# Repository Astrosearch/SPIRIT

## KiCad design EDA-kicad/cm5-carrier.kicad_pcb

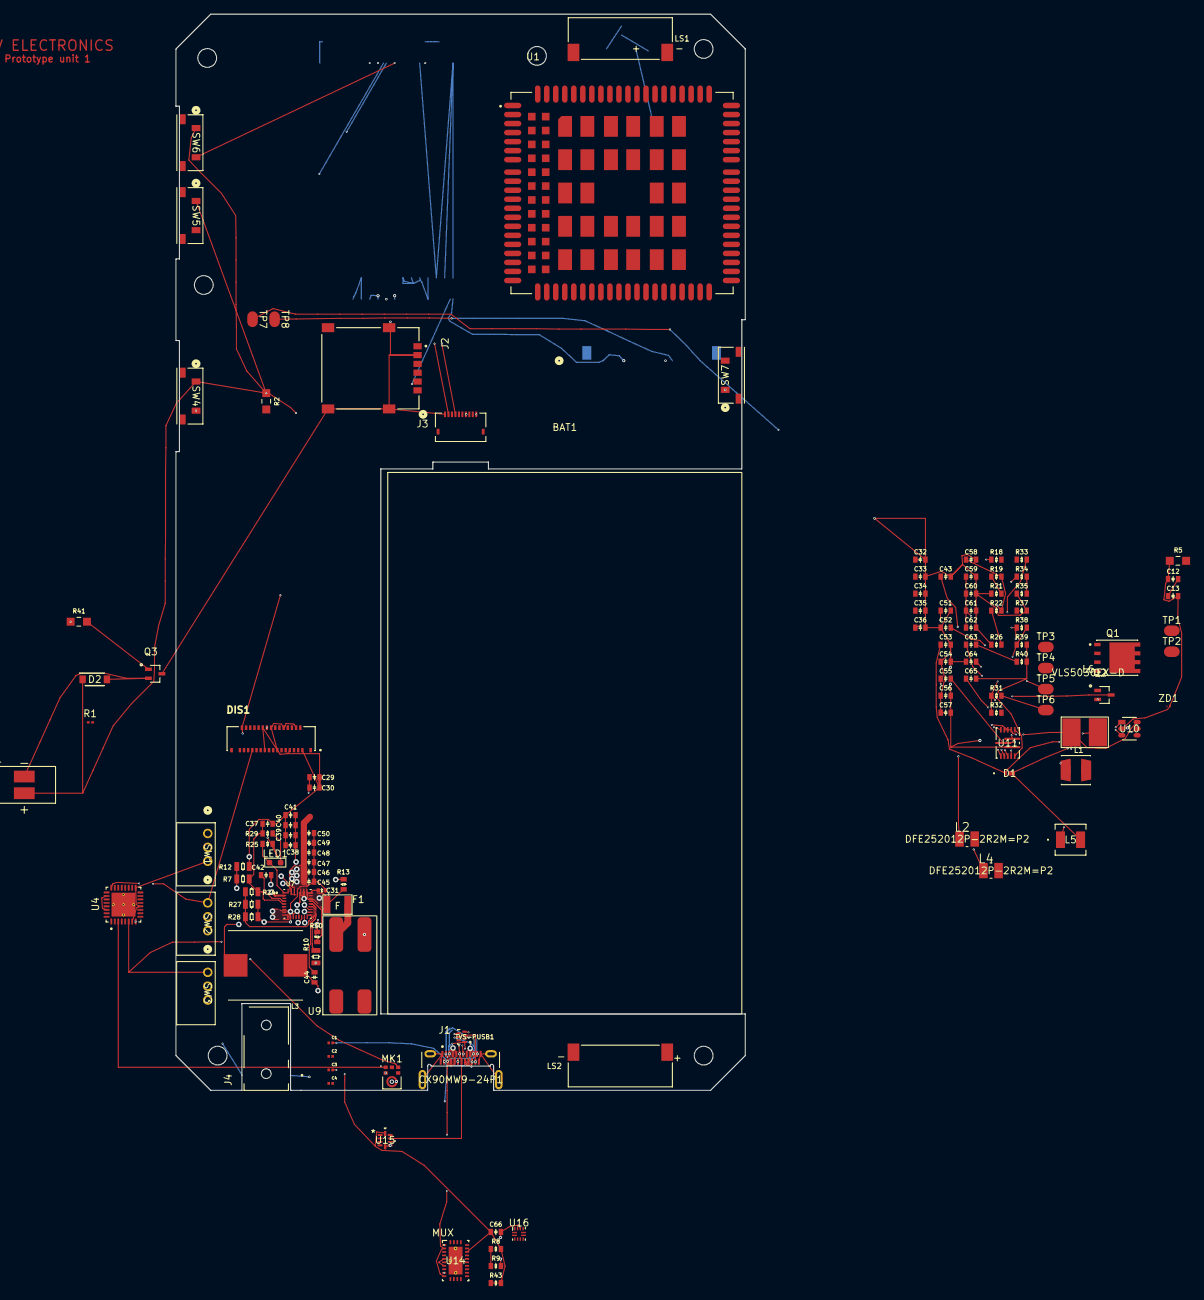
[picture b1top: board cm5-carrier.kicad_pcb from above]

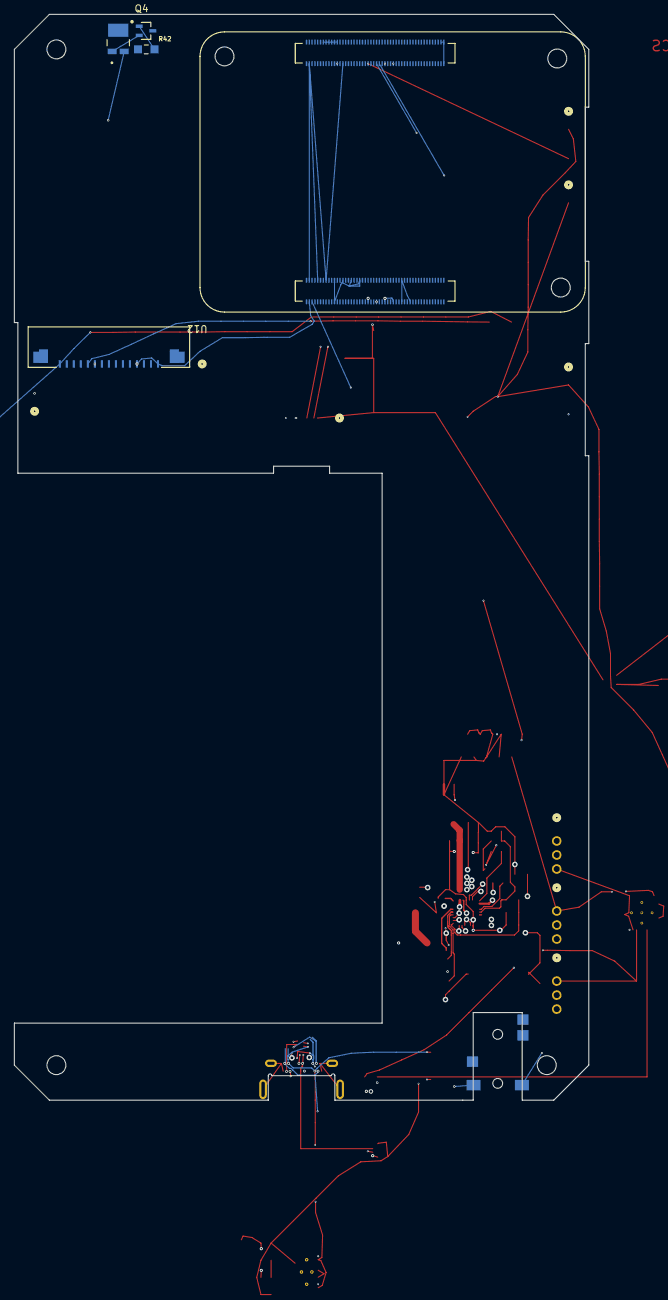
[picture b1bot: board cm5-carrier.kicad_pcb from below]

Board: 6 copper layers, 129 parts (5 on the bottom side), 118 nets.

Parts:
B1: VIBR; VIBRATION-PUI_HD-EMB1205-3-SC-R
BAT1: Li-ion-3.7 35Ah; battery_37V3500mAhLP685077JU
C1, C2, C3, C4: 0.33 µF coupling cap; USBC_capacitor_CAPC0603X33N
C12: 200pF; 0603-capacitor
C13, C38, C45, C55, C59, C66: 0.1uF; 0603-capacitor
C29, C30, C33, C34, C35, C39, C40, C41, C46, C47, C48, C49, C50: 10uF; 0603-capacitor
C31: 1nF 50V; 0402-capacitor
C32, C53, C54: 1uF; 0603-capacitor
C36, C43, C51, C56, C57, C58, C60, C61, C62, C65: 22uF; 0603-capacitor
C37, C52, C64: 4.7uF; 0603-capacitor
C42, C44: 47nF; 0603-capacitor
C63: 6.8nF; 0603-capacitor
D1: D_Schottky; schottky-diode-CR_DSN2_152AB-C_OSI
D2: 1N4007W-T; flyback-diode-SODFL3818X130N
DIS1: FH72-31S-0.3SHW; HRS_FH72-31S-0.3SHW
F1: 9A 6V; PTC RESET FUSE 9.0A 6V 1210 1210L900SLPR
J1: USBC-4-0-CX90MW9-24P1; USB-4-0-HIROSE_CX90MW9-24P1
J2: SIM-G85D1160022HHR; SIM-AMPHENOL_G85D1160022HHR
J3: FINGER; 10PIN
J4: SJ2-35894B-SMT-TR; 35mmJACK-CUI_SJ2-35894B-SMT-TR
L1: 3.3uH; 3-3uH-MURATA_LQH44PN3R3MPRL
L2, L4: 2.2uH; 2-2uH-inductor-INDC2520X120N
L3: 2.2uH; 2-2uh-inductorIND_ETQP4M2R2KVC
L5: 6.8uH; 6-8uH-inductor-LQH44PN6R8MPRLIND_LQH44PN_PR_MUR
L6: 1.5uH; 1-5uH-inductor-VLS5030EX-D
LED1: 5mA 2V Fv; LED-INDICATOR-RED-QBLP601-R5
LS1, LS2: CMR-15062S-67; SPEAKER_CMR-15062S-67
MK1: microphone; microphone_SPH0645LM4H-B
Module1: ComputeModule5-CM5; Raspberry-Pi-5-Compute-Module
Q1: NMOS-BSC0902NSIATMA1-PG-TDSON-8-6-IC_ISC037N03L5ISATMA1
Q2, Q3, Q4: gpio-driver-transistor-fix-SOT65P210X110-3N
R1: thermistor; thermistor-NTC0201Z_P63XP33_PAN
R2: 270KΩ 0.5W; 1K-05W-0805-RES_ERJP06J102V
R5: 100KΩ; 100K-0805-resistor-RES_ERA6AEB104V
R7: 127kΩ; 0805-resistor
R8, R9, R25, R30, R43: 10kΩ; 0603-resistor
R10: 4.7KΩ; 0805-resistor
R12: 100kΩ; 0805-resistor
R13: 100Ω; 0603-resistor
R18, R31, R32, R33: 100kΩ; 0603-resistor
R19: 680kΩ 1%; 0603-resistor
R21, R26: 470kΩ 1%; 0603-resistor
R22: 1MΩ 1%; 0603-resistor
R24: 5.23kΩ; 0805-resistor
R27: 10kΩ; 0805-resistor
R28: 30kΩ; 0805-resistor
R29: 680Ω; 0603-resistor
R34: 820kΩ; 0603-resistor
R35: 182KΩ; 0603-resistor
R37: 5Ω; 0603-resistor
R38: 750kΩ; 0603-resistor
R39: 200kΩ; 0603-resistor
R40: 6.8kΩ; 0603-resistor
R41, R42: 1KΩ 0.5W; 1K-05W-0805-RES_ERJP06J102V
SW1: EG25-switch-CSS-1210MC; privacy-switch-SW3_CSS-1210MC_NDC
SW2: MIC-switch-CSS-1210MC; privacy-switch-SW3_CSS-1210MC_NDC
SW3: CAM-switch-CSS-1210MC; privacy-switch-SW3_CSS-1210MC_NDC
SW4: PROG; buttonSW_TL3330_EWI
SW5: VOL-; buttonSW_TL3330_EWI
SW6: VOL+; buttonSW_TL3330_EWI
SW7: POW; buttonSW_TL3330_EWI
TP1, TP2, TP3, TP4, TP5, TP6, TP7, TP8: test-pad-1
TVS-PUSB1: TVS-array-IC_PUSB3AB6Z
U1: EG25GGC-128-SGNS; XCVR_EG25GGC-128-SGNS
U4: CODEC-TLV320AIC3204IRHBR; CODEC-QFN50P500X500X100-33N
U7: BQ25792RQMR; charger-bq25792-QFN40P400X400X100-29N
U9: BAT-CONNECTOR-FLTS22WR00
U10: 22V-boost-AP3032KTR-G1; SOT23-6_DIO
U11: MP3429GL-Z; QFN-3x4_MP3429_MNP
U12: FPC15pin-1mm-pitch-F52Q-1A7H1-11015; FPC15pin-1mm-pitch-CONN_F52Q-1A7H1-11015_AMP
U13: Flash-LED-Lumiled; LUMILED-DIODFN449X305X210-3N
U14: MUX HD3SS460RHRR; USB-MUX-RHR0028A
U15: USB SWITCH 2CHANNEL TS3USB221AQRSERQ1; USB-SWITCH-2CHANNEL-TS3USB221AQRSERQ1
U16: usb-polarity-TUSB321RWBR; polarity-usb-TUSB321RWBR
ZD1: protection-PESD5V0C1USFYL; USB-ESD-protection-diode-PESD5V0C1USFYL-SOD962-2_DSN0603-2_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

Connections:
1V8: DIS1.25, SW2.1, U4.24 (AVDD), U4.29 (DVDD)
3V3B: C66.1, DIS1.30, Module1.78 (GPIO_VREF(1.8v/3.3v_Input)), Q2.3 (S), R8.2, R25.2, R30.1, R31.1, R32.1, R33.2, R43.1, R43.2, SW3.1, U4.6 (IOVDD), U4.26 (LDOIN/HPVDD), U4.30 (LDO_SELECT), U14.22 (VCC), U15.10 (VCC)
5V: C59.1, C60.1, C61.1, C62.1, Module1.77 (+5v_(Input)), Module1.79 (+5v_(Input)), Module1.81 (+5v_(Input)), Module1.83 (+5v_(Input)), Module1.85 (+5v_(Input)), Module1.87 (+5v_(Input)), R38.1, U11.8 (VOUT), U16.12 (VDD)
22V: C53.1, D1.1 (K), DIS1.2, U10.5 (OV)
AGND: C65.2, R39.2, R40.2, U11.6 (AGND), U11.9 (FTY)
AUDIO_BCLK_I2S: MK1.4 (BCLK), Module1.49 (GPIO18), U4.2 (BCLK)
AUDIO_MCLK: Module1.54 (GPIO4), U4.1 (MCLK)
AUDIO_MIC_DATA: Module1.27 (GPIO20), U4.5 (DOUT/MFP2)
AUDIO_RESET: Module1.45 (GPIO24), U4.31 (~RESET)
AUDIO_SCL: Module1.28 (GPIO13), U4.9 (SCL/~SS), U12.13
AUDIO_SDA: Module1.31 (GPIO12), U4.10 (SDA/MOSI), U12.14
AUDIO_SOUND_DATA: Module1.25 (GPIO21), U4.4 (DIN/MFP1)
AUDIO_WCLK_I2S: MK1.1 (WS), Module1.26 (GPIO19), U4.3 (WCLK)
BACKLIGHT-: DIS1.31, R37.1, U10.3 (FB)
BAT+: C29.1, C30.1, F1.2, R13.2, U7.22 (BAT), U7.23 (BAT__1)
CAM SWITCH: Q2.2 (D), TP7.1 (A), U12.15
CAM_CK_N: Module1.127 (MIPI0_C_N), U12.8
CAM_CK_P: Module1.129 (MIPI0_C_P), U12.9
CAM_D0_N: Module1.115 (MIPI0_D0_N), U12.2
CAM_D0_P: Module1.117 (MIPI0_D0_P), U12.3
CAM_D1_N: Module1.121 (MIPI0_D1_N), U12.5
CAM_D1_P: Module1.123 (MIPI0_D1_P), U12.6
CAM_IO0: TP8.1 (A), U12.11
CC1: J1.A5 (CC1), Module1.94 (CC1)
CC2: J1.B5 (CC2), Module1.96 (CC2)
CHARGER D+: U7.6 (D+), U15.3 (2D+)
CHARGER D-: U7.7 (D-), U15.4 (2D-)
D+: J1.A6 (D1+), J1.B6 (D2+), TVS-PUSB1.5 (D+), U15.8 (D+)
D-: J1.A7 (D1-), J1.B7 (D2-), TVS-PUSB1.4 (D-), U15.7 (D-)
DEFDCDC1 DIVIDER: C36.1, L1.1, R34.1
DIS_SCL: DIS1.27, Module1.37 (GPIO7)
DIS_SDA: DIS1.26, Module1.30 (GPIO6)
DSI1_C_N: DIS1.11, Module1.187 (MIPI1_C_N)
DSI1_C_P: DIS1.12, Module1.189 (MIPI1_C_P)
DSI1_D0_N: DIS1.5, Module1.175 (MIPI1_D0_N)
DSI1_D0_P: DIS1.6, Module1.177 (MIPI1_D0_P)
DSI1_D1_N: DIS1.8, Module1.181 (MIPI1_D1_N)
DSI1_D1_P: DIS1.9, Module1.183 (MIPI1_D1_P)
DSI1_D2_N: DIS1.14, Module1.193 (MIPI1_D2_N)
DSI1_D2_P: DIS1.15, Module1.195 (MIPI1_D2_P)
DSI1_D3_N: DIS1.17, Module1.194 (MIPI1_D3_N)
DSI1_D3_P: DIS1.18, Module1.196 (MIPI1_D3_P)
GND: C12.1, C13.2, C29.2, C30.2, C31.2, C32.2, C33.2, C34.2, C35.2, C36.2, C37.2, C38.2, C39.2, C40.2, C41.2, C43.2, C45.2, C46.2, C47.2, C48.2, C49.2, C50.2, C51.2, C52.1, C53.2, C54.2, C56.2, C57.2, C58.2, C59.2, C60.2, C61.2, C62.2, C64.1, C66.2, DIS1.1, DIS1.4, DIS1.7, DIS1.10, DIS1.13, DIS1.16, DIS1.19, DIS1.20, J1.A1 (GND_A), J1.A12 (GND_A__1), J1.B1 (GND_B), J1.B12 (GND_B__1), J1.SH1 (SHIELD), J1.SH2 (SHIELD__1), J1.SH3 (SHIELD__2), J1.SH4 (SHIELD__3), J2.C5 (GND), J2.S1 (SHIELD_GND), J2.S2 (SHIELD_GND__1), J2.S3 (SHIELD_GND__2), J3.1, J4.1, MK1.2 (SELECT), MK1.3 (GND), Module1.1 (GND), Module1.2 (GND), Module1.3 (Ethernet_Pair3_P), Module1.8 (GND), Module1.13 (GND), Module1.14 (GND), Module1.22 (GND), Module1.23 (GND), Module1.32 (GND), Module1.33 (GND), Module1.42 (GND), Module1.43 (GND), Module1.52 (GND), Module1.53 (GND), Module1.59 (GND), Module1.60 (GND), Module1.65 (GND), Module1.66 (GND), Module1.71 (GND), Module1.74 (GND), Module1.98 (GND), Module1.107 (GND), Module1.108 (GND), Module1.113 (GND), Module1.114 (GND), Module1.119 (GND), Module1.120 (GND), Module1.125 (GND), Module1.126 (GND), Module1.131 (GND), Module1.132 (GND), Module1.137 (GND), Module1.138 (GND), Module1.144 (GND), Module1.150 (GND), Module1.155 (GND), Module1.156 (GND), Module1.161 (GND), Module1.162 (GND), Module1.167 (GND), Module1.168 (GND), Module1.173 (GND), Module1.174 (GND), Module1.179 (GND), Module1.180 (GND), Module1.185 (GND), Module1.186 (GND), Module1.191 (GND), Module1.192 (GND), Module1.197 (GND), Module1.198 (GND), Q3.3 (S), Q4.3 (S), R5.1, R9.2, R10.1, R12.2, R21.1, R26.1, R27.2, R28.2, R35.1, R37.2, SW1.3, TVS-PUSB1.2 (GND), U4.7 (IOVSS), U4.12 (SPI_SELECT), U4.17 (AVSS), U4.28 (DVSS), U4.33 (EP), U7.10 (ACDRV2), U7.11 (ACDRV1), U7.13 (~CE), U7.27 (GND), U9.4 (OUT-), U10.2 (GND), U11.7 (PGND), U12.1, U12.4, U12.10, U14.29 (PAD_GND), U15.5 (GND), U15.6 (~OE), U16.10 (GND), ZD1.2
GPIO2: Module1.58 (GPIO2), SW7.2
GPIO3: Module1.56 (GPIO3), SW6.2
GPIO15: Module1.51 (GPIO15), SW5.2
GPIO17: Module1.50 (GPIO17), SW4.2
GPIO22: Module1.46 (GPIO22), R42.1
GPIO27: Module1.48 (GPIO27), R41.1
JACK-IN: J4.10, Module1.41 (GPIO25)
JACK_MIC: J4.4, U4.8 (SCLK/MFP3)
LCD_PWM: Module1.55 (GPIO14), U10.4 (CTRL)
MIC-SWITCH: C12.2, C13.1, MK1.5 (VDD), SW2.2
MUX POL: U14.3 (POL), U16.11 (DIR)
unnamed: C63.2, R40.1
unnamed: D1.2 (A), L5.2, U10.1 (SW)
unnamed: J3.8, R2.2
unnamed: LED1.2 (A), R29.1
unnamed: LED1.1 (K), R25.1, U7.1 (STAT)
unnamed: MK1.6 (DATA_OUT), R5.2
unnamed: C1.1, Module1.157 (USB3-1-RX_N)
unnamed: C2.1, Module1.159 (USB3-1-RX_P)
unnamed: C3.1, Module1.169 (USB3-1-TX_N)
unnamed: C4.1, Module1.171 (USB3-1-TX_P)
unnamed: Q2.1 (G), SW3.2
unnamed: B1.N, D2.2, Q3.2 (D)
unnamed: Q3.1 (G), R41.2
unnamed: Q4.2 (D), U13.1 (-)
unnamed: Q4.1 (G), R42.2
unnamed: C52.2, TP5.1 (A)
unnamed: R13.1, U7.18 (BATP)
unnamed: C42.2, U7.4 (BTST1)
unnamed: C44.2, U7.19 (BTST2)
unnamed: R7.1, R12.1, U7.17 (ILIM_HIZ)
unnamed: C38.1, C39.1, C40.1, C41.1, U7.29 (PMID)
unnamed: R10.2, U7.20 (PROG)
unnamed: C31.1, U7.24 (SDRV)
unnamed: C42.1, L3.2, U7.28 (SW1)
unnamed: C44.1, L3.1, U7.26 (SW2)
unnamed: R24.2, R27.1, R28.1, U7.16 (TS)
unnamed: R34.2, R35.2
unnamed: R22.1, R26.2
unnamed: R19.1, R21.2
unnamed: C32.1, R18.1
unnamed: C43.1, L2.1
unnamed: C51.1, L4.1
unnamed: F1.1, U9.3 (OUT+)
unnamed: C55.1, U11.13 (BST)
unnamed: C63.1, U11.4 (COMP)
unnamed: R38.2, R39.1, U11.5 (FB)
unnamed: C65.1, U11.3 (SS)
unnamed: C55.2, L6.2, U11.1 (SW)
unnamed: C64.2, U11.2 (VDD)
unnamed: R8.1, R9.1, U14.8 (AMSEL)
REGN: C37.1, R7.2, R24.1, R29.2, U7.5 (REGN)
RX1+: C2.2, J1.A11 (RX2+), J1.B11 (RX1+), TVS-PUSB1.7 (RX+), U14.1 (CRX1P), U14.9 (CRX2P)
RX1-: C1.2, J1.A10 (RX2-), J1.B10 (RX1-), TVS-PUSB1.6 (Rx-), U14.2 (CRX1N), U14.10 (CRX2N)
SCL PWR: Module1.80 (SCL0), U7.14 (SCL)
SDA PWR: Module1.82 (SDA0), U7.15 (SDA)
SPI0_CLK: J3.2, Module1.38 (GPIO11)
SPI0_CS: J3.5, Module1.39 (GPIO8)
SPI0_MISO: J3.3, Module1.40 (GPIO9)
SPI0_MOSI: J3.4, Module1.44 (GPIO10)
SPI0_RDY: J3.6, Module1.34 (GPIO5)
SSRX+: Module1.130 (USB3-0-RX_P), U14.28 (SSRXP)
SSRX-: Module1.128 (USB3-0-RX_N), U14.27 (SSRXN)
SSTX+: Module1.142 (USB3-0-TX_P), U14.26 (SSTXP)
SSTX-: Module1.140 (USB3-0-TX_N), U14.25 (SSTXN)
SYS: C45.1, C46.1, C47.1, C48.1, C49.1, C50.1, C54.1, C56.1, C57.1, C58.1, L5.1, L6.1, R19.2, R22.2, SW1.1, U7.25 (SYS), U10.6 (VIN), U11.10 (MODE), U11.11 (EN), U11.12 (VIN)
SYS D+: Module1.163 (USB3-1-D_P), U15.1 (1D+)
SYS D-: Module1.165 (USB3-1-D_N), U15.2 (1D-)
TX1+: C4.2, J1.A2 (TX1+), J1.B2 (TX2+), TVS-PUSB1.3 (Tx+), U14.4 (CTX1P), U14.6 (CTX2P)
TX1-: C3.2, J1.A3 (TX1-), J1.B3 (TX2-), TVS-PUSB1.1 (Tx-), U14.5 (CTX1N), U14.7 (CTX2N)
USB SWITCH: Module1.47 (GPIO23), U15.9 (S)
USBC POW: J1.A4 (VBUS_A), J1.A9 (VBUS_A__1), J1.B4 (VBUS_B), J1.B9 (VBUS_B__1), U7.2 (VBUS), U7.8 (VAC2), U7.9 (VAC1), ZD1.1
VCC: B1.P, D2.1, J3.7, J3.10, R2.1, SW4.1, SW5.1, SW6.1, SW7.1, U13.2 (+)
~BQ INT: R30.2, U7.21 (~INT)
~TPS INT: R31.2, TP6.1 (A)
